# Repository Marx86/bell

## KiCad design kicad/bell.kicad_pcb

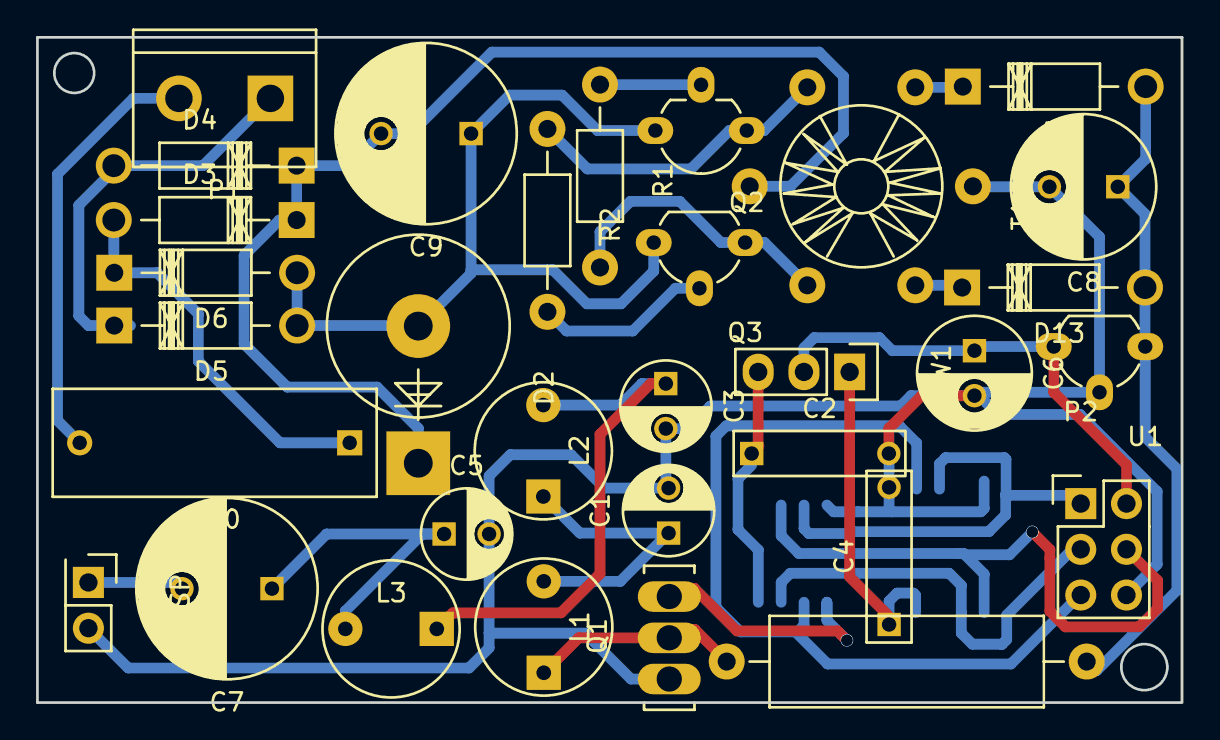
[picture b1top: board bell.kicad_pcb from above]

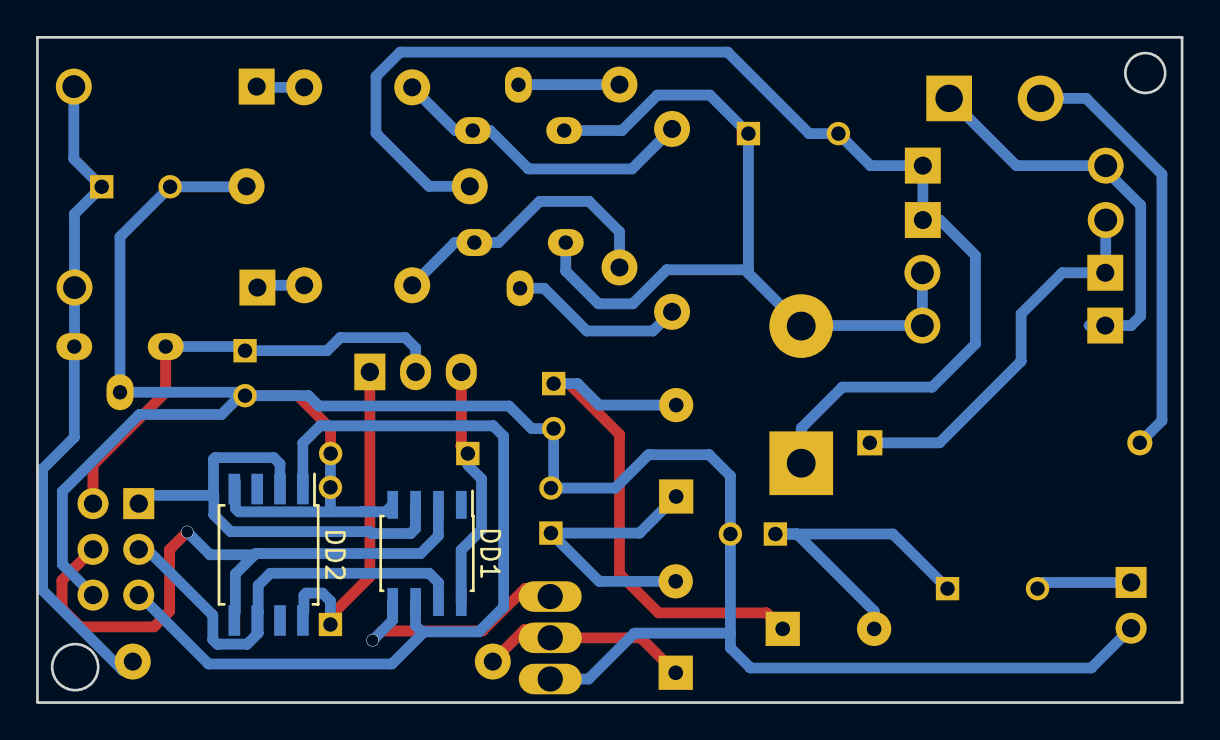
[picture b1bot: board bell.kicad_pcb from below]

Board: 2 copper layers, 63.6 x 37.0 mm, 34 parts (2 on the bottom side), 26 nets.

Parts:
C1: 2.2; C_Radial_D5_L11_P2.5
C2, C4: 0.1; C_Rect_L10_W2.5_P5
C3, C5: 1.0; C_Radial_D5_L11_P2.5
C6: 10.0; C_Radial_D6.3_L11.2_P2.5
C7: 100.0; C_Radial_D10_L16_P5
C8: 470.0; C_Radial_D8_L13_P3.8
C9: 22.0; C_Radial_D10_L21_P5
C10: 2.2; C_Rect_L18_W6_P15
D1, D13: DIODESCH; Diode_DO-41_SOD81_Horizontal_RM10
D2: Д816Г; Diode_P600_Vertical_KathodeUp
D3, D4, D5, D6: 1N4007; Diode_DO-41_SOD81_Horizontal_RM10
DD1: ATTINY13A-SS; SOIC-8_3.9x4.9mm_Pitch1.27mm
DD2: w25q64fvssig; SOIJ-8_5.3x5.3mm_Pitch1.27mm
L1: 150 uH; INDUCTOR_V
L2, L3: 20 uH; INDUCTOR_V
P1: CONN_2; bornier2
P2: CONN_3X2; Pin_Header_Straight_2x03
Q1: BD137; SOT126_SOT32_Housing_Vertical_BigPads
Q2: КТ313; TO-92_Molded_Wide_Oval_Reverse
Q3: КТ313; TO-92_Molded_Wide_Oval
R1, R2: 5.1 k; Resistor_Horizontal_RM10mm
R3: 5.1; Resistor_Horizontal_RM20mm
SP1: SPEAKER; Pin_Header_Straight_2x01
SW1: SWITCH_INV; Pin_Header_Straight_1x03
T1: TRANSFO_4; Transformer_Toroid_Tapped_horizontal_Diameter9mm_Amidon-T30
U1: LM7805CT; TO-92_Molded_Wide_Oval

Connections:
+5V: C8.1, D1.2, D13.2, R3.1, U1.1
GNDPWR: C1.2, C2.2, C3.2, C4.2, C5.2, C6.2, C8.2, DD1.4, DD2.4, P2.6, Q1.1, SP1.2, T1.5, U1.2
unnamed: C1.1, L1.2, L2.1
unnamed: C2.1, DD1.8, SW1.3
unnamed: C3.1, L2.2, L3.1
unnamed: C4.1, DD2.8, SW1.1
unnamed: C5.1, C7.1, L3.2
unnamed: C7.2, SP1.1
unnamed: C9.1, D2.2, D5.2, D6.2, Q2.3, Q3.3
unnamed: C9.2, D2.1, D3.1, D4.1, T1.2
unnamed: C10.1, D3.2, D6.1
unnamed: C10.2, P1.2
unnamed: D1.1, T1.4
unnamed: D4.2, D5.1, P1.1
unnamed: D13.1, T1.6
unnamed: DD1.2, DD2.5, P2.4
unnamed: DD1.3, DD2.2, P2.1
unnamed: DD1.5, Q1.3
unnamed: DD1.6, DD2.1, P2.5
unnamed: DD1.7, DD2.6, P2.3
unnamed: L1.1, Q1.2, R3.2
unnamed: Q2.1, R2.1, T1.1
unnamed: Q2.2, R1.1
unnamed: Q3.1, R1.2, T1.3
unnamed: Q3.2, R2.2
VDD: C6.1, P2.2, SW1.2, U1.3

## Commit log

2016-07-25 Init
2016-07-29 Add board
2016-08-04 Board
